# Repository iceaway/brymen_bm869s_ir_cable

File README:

NOTE
==============
This repo has been cloned with permission from its original author at 
https://git.e1e0.net/brymen_bm869s_ir_cable.git

The modifications I made were to make it work with an attiny84a MCU which I 
happened to have available. The schematic has been updated to reflect this 
as well.
==============

# Brymen 869s Serial cable

BOM:

  * micro controller ATTiny85
  * One infrared diode.
  * One photodiode.
  * 3 resistors (75R 4k7 2k)
  * One NPN BJT (like the 2N2222A)
  * A usb to serial adapter that can provid 5v.

I built it on a perfboard, so no pcb design is provided.

The 3D desigh fits perfectly and leaves 48 x 11 mm (more or less) of
space for the pcb. An STL file can be found at (in case you don't know
how to use FreeCAD):

https://onna.be/files/brymen_cable_attachemnt_v2.stl

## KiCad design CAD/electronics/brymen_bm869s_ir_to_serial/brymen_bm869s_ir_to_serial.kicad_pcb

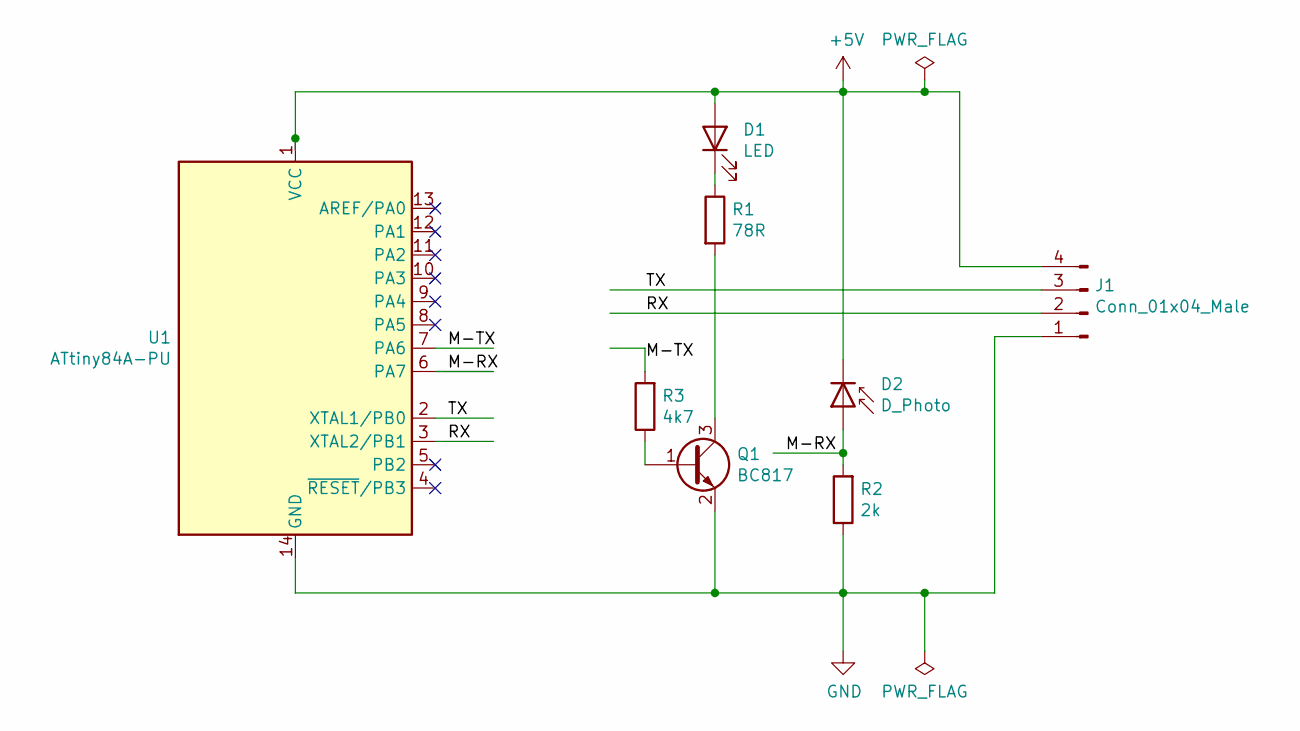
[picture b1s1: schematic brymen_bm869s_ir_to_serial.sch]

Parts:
D1: LED; LED_D4.0mm
D2: D_Photo; LED_D4.0mm
J1: Conn_01x04_Male; PinHeader_1x04_P2.54mm_Vertical
Q1: BC817; SOT-23
R1: 78R; R_0603_1608Metric
R2: 2k; R_0603_1608Metric
R3: 4k7; R_0603_1608Metric
U1: ATtiny84A-PU; DIP-14_W7.62mm

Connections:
+5V: D1.2 (A), D2.1 (K), J1.4, U1.1 (VCC)
/M-RX: D2.2 (A), R2.2, U1.6 (PA7)
/M-TX: R3.2, U1.7 (PA6)
/RX: J1.2, U1.3 (XTAL2/PB1)
/TX: J1.3, U1.2 (XTAL1/PB0)
GND: J1.1, Q1.2 (E), R2.1, U1.14 (GND)
unnamed: D1.1 (K), R1.1
unnamed: Q1.1 (B), R3.1
unnamed: Q1.3 (C), R1.2

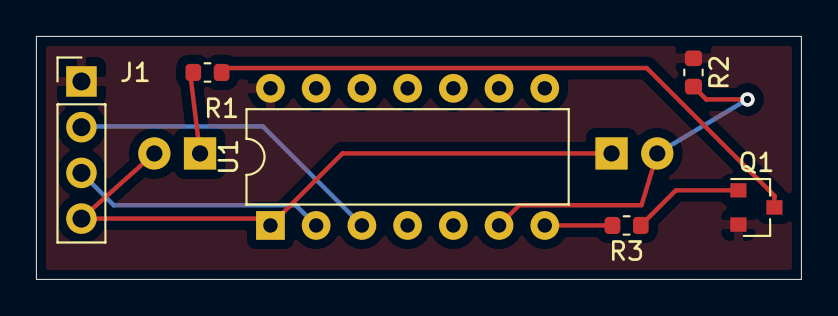
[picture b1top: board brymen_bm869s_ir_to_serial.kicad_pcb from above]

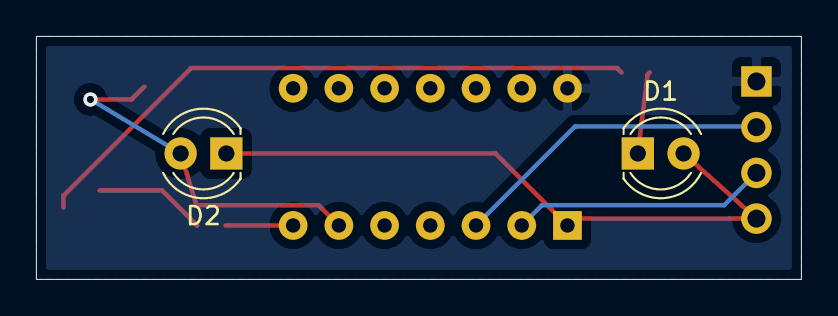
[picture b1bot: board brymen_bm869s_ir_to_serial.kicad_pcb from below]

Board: 2 copper layers, 42.5 x 13.5 mm, 8 parts (2 on the bottom side), 9 nets.

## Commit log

2018-12-03 initial version
2018-12-03 refining shape to test better fit.
2018-12-03 trying for better fit with dimensions from EEVblog forum
2018-12-04 schematic
2018-12-04 firmware first version
2018-12-05 better name for main program and cleaning makefile
2018-12-05 ignoring compilation products
2018-12-05 first working version + some comments and small fixes
2018-12-05 cosmetic changes to c file
2018-12-05 final 3d model version
2018-12-08 giving some credit
2018-12-08 removing hex file, this should be generated
2018-12-08 ignoring hex files
2018-12-08 small readme
2020-08-27 Modified code to be work with an attiny84a MCU
2020-08-29 Added a PCB design, but it has not been verified.
2020-11-24 changes...?
2020-11-25 Wrong distance between the IR-diodes, would not fit in the enclosure.
2020-11-25 Something changed apparantly
